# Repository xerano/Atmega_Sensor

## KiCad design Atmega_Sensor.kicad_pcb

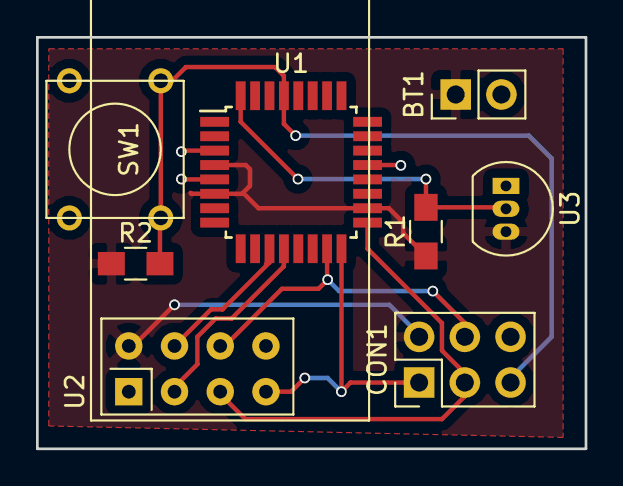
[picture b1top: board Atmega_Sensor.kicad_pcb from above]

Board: 2 copper layers, 30.5 x 22.9 mm, 8 parts (0 on the bottom side), 9 nets.

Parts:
BT1: Battery; Pin_Header_Straight_1x02_Pitch2.54mm
CON1: AVR-ISP-6; Pin_Header_Straight_2x03_Pitch2.54mm
R1: 4K7; R_0805_HandSoldering
R2: 10K; R_0805_HandSoldering
SW1: SW_Push; SW_PUSH_SMALL
U1: ATMEGA328P-AU; TQFP-32_7x7mm_Pitch0.8mm
U2: NRF24L01_Breakout; nRF24L01_Breakout
U3: DS18B20; TO-92_Inline_Narrow_Oval

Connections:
+3V3: BT1.1, CON1.2, R1.1, R2.1, U1.4, U1.6, U1.18, U2.2, U3.3
CE: U1.12, U2.3
CSN: U1.11, U2.4
GND: BT1.2, CON1.6, SW1.2, U1.3, U1.5, U1.21, U2.1, U3.1
MISO: CON1.1, U1.16, U2.7
MOSI: CON1.4, U1.15, U2.6
unnamed: R1.2, U1.32, U3.2
RST: CON1.5, R2.2, SW1.1, U1.29
SCK: CON1.3, U1.17, U2.5
